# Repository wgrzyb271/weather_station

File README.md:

# 🌡️ ESP32-C6 Indoor Weather Station

An open-source indoor environmental monitoring system built on a custom **ESP32-C6-WROOM-1** dev board. It measures temperature, relative humidity, barometric pressure, and air quality (IAQ) using the **Bosch BME680**, displaying real-time metrics on a color TFT screen with dynamic, flicker-free backlight dimming.

Designed using **KiCad** for hardware development and programmed via **PlatformIO**.

---

## ✨ Features

* **Environmental Sensing:** High-accuracy indoor temperature, humidity, barometric pressure, and Gas/IAQ metrics via Bosch BME680.
* **Dynamic Backlight Control:** Ambient light-sensing using a photoresistor (LDR) voltage divider coupled with high-frequency PWM.
* **IEEE 1789 Compliant Dimming:** Backlight PWM frequency tuned to prevent visible flicker and health risks associated with LED dimming, as outlined in the IEEE 1789-2015 standard.
* **Custom Hardware:** Tailored PCB designed from scratch around the ESP32-C6 module.
* **TFT Display UI:** Real-time data visualization on a vibrant color LCD screen.
* **3D-Printed Enclosure:** Protective cover for the circuit designed in **FreeCAD**, sized to fit the custom PCB and TFT cutout.

---

## 🛠️ Hardware Overview

| Component | Details |
|---|---|
| **Microcontroller** | ESP32-C6-WROOM-1 (RISC-V 32-bit single-core, Wi-Fi 6, Bluetooth 5, 802.15.4 / Thread / Zigbee) |
| **Environmental Sensor** | Bosch BME680 (I2C) |
| **Display** | ST7735 TFT Display (SPI) |
| **Light Sensing** | Photoresistor (LDR) in a voltage divider network connected to an ESP32-C6 ADC pin |
| **Backlight Control** | TFT backlight pin driven directly via the ESP32-C6 **LEDC (LED Control)** peripheral to generate high-frequency PWM for IEEE 1789-compliant dimming |

---

## 💻 Tech Stack & Libraries

* **EDA / Hardware:** [KiCad](https://www.kicad.org/) (Schematics & PCB Layout)
* **3D CAD / Enclosure:** [FreeCAD](https://www.freecad.org/) (Circuit cover / enclosure design)
* **Firmware Framework:** [PlatformIO](https://platformio.org/) on Arduino Core
* **Core Libraries:**
  * `Adafruit_ST7735` & `Adafruit_GFX` – Display driver and graphics library
  * `Adafruit_BME680` & `Adafruit_Sensor` – Environmental sensor driver
  * `Wire.h` & `SPI.h` – Hardware bus communication

---

## 📋 Project Management

This project is managed using [Plane](https://app.plane.so) — an open-source Jira/Confluence alternative — for issue tracking, sprints, and documentation. Feature requests, bugs, and task boards live there rather than solely in GitHub Issues.

---

## 🗺️ Roadmap / Planned Features

* **Zephyr RTOS Port:** Migrate firmware from Arduino Core to Zephyr RTOS for improved power management, native threading, and better long-term driver support on the ESP32-C6.
* **MQTT Broker Integration:** Publish sensor readings (temperature, humidity, pressure, IAQ) to an MQTT broker, with support for **Home Assistant** MQTT auto-discovery.
* **OTA Firmware Updates:** Over-the-air update support to avoid re-flashing over USB for field-deployed units.
* **Web Configuration Portal:** Captive-portal Wi-Fi provisioning and settings UI served directly from the ESP32-C6.
* **Historical Data Logging:** Local logging (SD card or flash) with optional export/graphing.

> Have a feature request? Open an [issue](../../issues) or start a [discussion](../../discussions).

---

## 🚀 Getting Started

### 1. Hardware Design

Schematics, PCB layout files, and BOM (Bill of Materials) can be found in the [`/hardware`](./hardware) directory. Open them with **KiCad 10.0+**.

### 2. Firmware Compilation

1. Install [Visual Studio Code](https://code.visualstudio.com/) and the [PlatformIO extension](https://platformio.org/platformio-ide).
2. Clone this repository:
   ```bash
   git clone https://github.com/your-username/your-repo-name.git
   cd your-repo-name
   ```
3. Open the project folder in VS Code — PlatformIO should detect the `platformio.ini` automatically and install the required libraries and toolchain.
4. Connect the ESP32-C6-WROOM-1 board via USB.
5. Build and upload:
   ```bash
   pio run --target upload
   ```
6. Monitor serial output:
   ```bash
   pio device monitor
   ```

---

## 📁 Repository Structure

```
.
├── hardware/        # KiCad schematics, PCB layout, and BOM
├── enclosure/        # FreeCAD source files and exported STL/STEP for the cover
├── src/              # Firmware source code
├── include/          # Header files
├── lib/               # Project-specific libraries
├── platformio.ini    # PlatformIO project configuration
└── README.md
```

---

## 🤝 Contributing

Contributions, issues, and feature requests are welcome. Feel free to check the [issues page](../../issues) or submit a pull request.

---

## 📄 License

This project is licensed under the terms of the license included in this repository — see [`LICENSE`](./LICENSE) for details.

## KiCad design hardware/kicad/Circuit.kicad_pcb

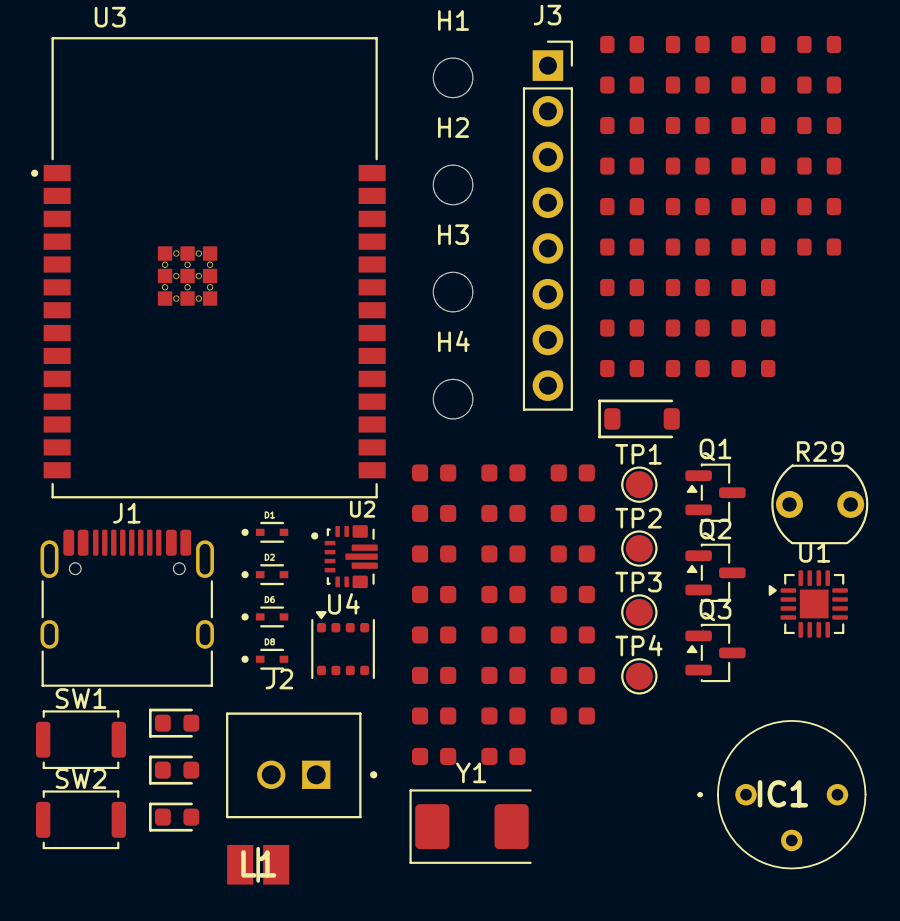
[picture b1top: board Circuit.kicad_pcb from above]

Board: 2 copper layers, 88 parts (0 on the bottom side), 53 nets, no tracks yet.

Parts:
C1, C10, C15, C19: 1uF; C_0603
C2, C3, C5: 4.7uF; C_0603
C4, C6: 2.2uF; C_0603
C7, C8, C9, C16: 10uF; C_0603
C11, C13, C14, C17, C18, C20, C23: 100nF; C_0603
C12: 22uF; C_0603
C21, C22: 12pF; C_0603
D1, D2, D6, D8: LESD5D5.0CT1G; TVS_LESD5D5.0CT1G
D3: Green; D_0603
D4: Red; D_0603
D5: BZT52C6V2; D_SOD-123
D7: Blue; D_0603
H1, H2, H3, H4: MountingHole; MountingHole_2.2mm_M2
IC1: AS312
J1: USB_C_Receptacle_USB2.0_14P; USB_C_Receptacle_HRO_TYPE-C-31-M-12
J2: B2B-XH-A__LF__SN_; JST_B2B-XH-A__LF__SN_
J3: Conn_01x08_Socket; PinSocket_1x08_P2.54mm_Vertical
L1: 1.5uH 4A; INDC2520X100N
Q1, Q2: AO3401A; SOT-23
Q3: AO3400A; SOT-23
R1: 75K; R_0603
R2: 1.6K; R_0603
R3: 1.78K; R_0603
R4, R5: 5k1; R_0603
R6, R14: 470K; R_0603
R7, R8: 1.5K; R_0603
R9, R10, R11, R12, R16, R21, R22, R25, R26: 100K; R_0603
R13, R18, R19, R20, R24: 10K; R_0603
R15: 150K; R_0603
R17: 1K; R_0603
R23: 220; R_0603
R27: 330; R_0603
R28, R31, R32: 4.7K; R_0603
R29: R_Photo; R_LDR_5.1x4.3mm_P3.4mm_Vertical
R30: 30K; R_0603
R33: 10M; R_0603
SW1, SW2: SW_Push; SW_Push_SPST_NO_Alps_SKRK
TH1: 10K; R_0603
TP1: TP_SYS; TestPoint_Pad_D1.5mm
TP2: TP_VBUS; TestPoint_Pad_D1.5mm
TP3, TP4: TP_+3V3; TestPoint_Pad_D1.5mm
U1: BQ24075RGT; VQFN-16-1EP_3x3mm_P0.5mm_EP1.6x1.6mm
U2: TPS63070RNMR; VREG_TPS63070RNMR
U3: ESP32-C6-WROOM-1-N8; XCVR_ESP32-C6-WROOM-1-N8
U4: BME680; Bosch_LGA-8_3x3mm_P0.8mm_ClockwisePinNumbering
Y1: 32.768 kHz; Crystal_SMD_0603-2Pin_6.0x3.5mm

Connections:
+3.3V: C8.1, C12.1, C16.2, C17.2, C18.2, C19.1, C20.1, C23.1, D8.2, IC1.1 (VDD), J3.6, R14.1, R16.1, R17.1, R20.1, R27.1, R28.2, R29.1, R31.1, R32.1, TP3.1 (1_1), U2.7_8 (VOUT), U3.2 (3V3), U4.2 (CSB), U4.6 (VDDIO), U4.8 (VDD)
+5V: C1.1, C2.2, C6.2, D5.1, D6.2, Q1.2 (S), R25.1, TP2.1 (1_1), U1.13 (IN)
BAT: C5.1, J2.1, Q2.2 (S), R11.1, U1.2 (BAT), U1.3 (BAT)
BAT_ADC: C10.2, C11.2, R9.2, R10.1, U3.26 (IO3)
BAT_CTRL: R12.1, U3.12 (IO11)
BL: J3.7, Q3.3 (D), R28.1
CHG_EN1: R21.1, U1.6 (EN1), U3.27 (IO2)
CHG_EN2: R22.1, U1.5 (EN2), U3.24 (RXD0/GPIO17)
D+: D2.2, J1.A6 (D+), J1.B6 (D+), U3.14 (IO13)
D-: D1.2, J1.A7 (D-), J1.B7 (D-), U3.13 (IO12)
DPM_OUT: C3.1, C7.1, C9.1, D3.2, D4.2, R13.1, TP1.1 (1_1), U1.10 (OUT), U1.11 (OUT), U2.12_13 (VIN)
FB: R14.2, R15.1, U2.5 (FB)
GND: C1.2, C2.1, C3.2, C4.1, C5.2, C6.1, C7.2, C8.2, C9.2, C10.1, C11.1, C12.2, C13.2, C14.2, C15.2, C16.1, C17.1, C18.1, C19.2, C20.2, C21.1, C22.1, C23.2, D1.1, D2.1, D6.1, D8.1, IC1.3 (VSS), J1.A1 (GND), J1.A12 (GND), J1.B1 (GND), J1.B12 (GND), J1.SH (SHIELD), J2.2, J3.8, Q3.2 (S), R1.1, R4.2, R5.2, R6.2, R10.2, R15.2, R19.2, R21.2, R22.2, R24.1, R26.2, R30.1, SW1.1, SW2.2, TH1.2, U1.8 (VSS), U1.17 (VSS), U2.4 (GND), U2.6 (FB2), U2.10 (PGND), U2.15 (VSEL), U3.1 (GND), U3.28 (GND), U3.29_1 (GND), U3.29_2 (GND), U3.29_3 (GND), U3.29_4 (GND), U3.29_5 (GND), U3.29_6 (GND), U3.29_7 (GND), U3.29_8 (GND), U3.29_9 (GND), U4.1 (GND), U4.5 (SDO), U4.7 (GND)
LDR: R29.2, R30.2, U3.4 (IO4)
unnamed: D3.1, R7.1
unnamed: D4.1, R8.1
unnamed: D7.2, R27.2
unnamed: IC1.2 (REL), R18.2, R19.1
unnamed: J1.A5 (CC1), R5.1
unnamed: J1.B5 (CC2), R4.1
unnamed: J1.A4 (VBUS), J1.A9 (VBUS), J1.B4 (VBUS), J1.B9 (VBUS), Q1.3 (D)
unnamed: C4.2, D5.2, Q1.1 (G), R6.1
unnamed: Q2.3 (D), R9.1
unnamed: Q2.1 (G), R11.2, R12.2
unnamed: Q3.1 (G), R23.2, R24.2
unnamed: R2.2, U1.12 (ILIM)
unnamed: R3.2, U1.16 (ISET)
unnamed: R2.1, R3.1, U1.4 (~CE), U1.15 (SYSOFF)
unnamed: R1.2, U1.14 (TMR)
unnamed: TH1.1, U1.1 (TS)
unnamed: R13.2, U2.1 (PS/SYNC), U2.14 (EN)
unnamed: L1.2, U2.11 (L1)
unnamed: L1.1, U2.9 (L2)
unnamed: C13.1, U2.3 (VAUX)
unnamed: C14.1, C15.1, R20.2, SW1.2, U3.3 (EN)
unnamed: R17.2, U3.10 (IO8)
unnamed: SW2.1, U3.15 (IO9)
unnamed: D7.1, U3.16 (IO18)
PG: R16.2, U2.2 (PG)
PIR: R18.1, U3.17 (IO19)
PWM: R23.1, U3.23 (IO15)
S_SCL: R32.2, U3.7 (IO7), U4.4 (SCK)
S_SDA: R31.2, U3.6 (IO6), U4.3 (SDI)
TFT_CLK: J3.5, U3.18 (IO20)
TFT_CS: J3.2, U3.11 (IO10)
TFT_DIN: J3.4, U3.19 (IO21)
TFT_D/C: J3.3, U3.20 (IO22)
TFT_RST: J3.1, U3.21 (IO23)
VBUS_SENSE: R25.2, R26.1, TP4.1 (1_1), U3.5 (IO5)
XTAL_N: C21.2, R33.2, U3.9 (IO1), Y1.1
XTAL_P: C22.2, R33.1, U3.8 (IO0), Y1.2
~CHG: R8.2, U1.9 (~CHG)
~PGOOD: R7.2, U1.7 (~PGOOD)

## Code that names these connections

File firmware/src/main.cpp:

#include <Arduino.h>
#include <Wire.h>
#include <SPI.h>
#include <cstdio>
#include <cmath>
#include <Adafruit_GFX.h>
#include <Adafruit_ST7735.h>
#include <Adafruit_Sensor.h>
#include <Adafruit_BME680.h>

// --- PIN DEFINITIONS ---
#define TFT_SCLK  19
#define TFT_MOSI  18
#define TFT_CS    21
#define TFT_DC    16
#define TFT_RST   17

#define ADC_PIN   0
#define BL_PIN    1

// --- HARDWARE SPECIFIC ADC SETTINGS (LDR pull-up / resistor pull-down divider) ---
// Wiring: Vcc -> LDR -> ADC_PIN -> R_pulldown -> GND
// Bright light = LDR resistance drops   = node pulled toward Vcc  = HIGH raw ADC
// Dark room    = LDR resistance rises   = node pulled toward GND  = LOW raw ADC
#define ADC_RAW_DARK    150   // Adjust based on Serial log reading in total darkness
#define ADC_RAW_BRIGHT  3600  // Adjust based on Serial log reading under bright light

// --- IEEE 1789 & HARDWARE PWM CONFIGURATION ---
// IEEE Std 1789-2015 does NOT define a single "safe" frequency - it defines a
// risk curve relating modulation frequency to percent flicker (modulation depth):
//   < 90 Hz            : high risk region, avoid regardless of depth
//   90 Hz  - 1250 Hz    : acceptable only at reduced modulation depth
//   > 1250-3000 Hz      : commonly cited as the "low risk / no observable effect"
//                         band even near 100% modulation depth, since above
//                         ~3 kHz the frequency is well past where stroboscopic
//                         and phantom-array effects remain perceptible.
// 24 kHz PWM Frequency:
// 1. Clears every published threshold above (1250 Hz / 2000 Hz / 3000 Hz) by
//    an 8-24x margin, independent of the exact modulation depth achieved below.
// 2. Sits safely above 20 kHz, the traditional edge of adult human hearing,
//    giving margin against audible coil/capacitor whine (20 kHz itself is
//    borderline - some younger listeners perceive close to that edge).
#define PWM_FREQ          24000  // 24 kHz (comfortable margin above IEEE 1789 low-risk band and audible range)
#define PWM_RES           8      // 8-bit resolution (0 - 255)
#define PWM_MAX           190    // Maximum duty cycle value (for 8-bit resolution)
#define PWM_MIN_THRESHOLD 15     // Duty cycle floor (prevents display dropouts).
                                 // NOTE: this caps modulation depth at ~88.9%
                                 // (Percent Flicker = 100*(PWM_MAX-15)/(PWM_MAX+15)),
                                 // not full 0-100% - a small extra safety
                                 // margin on top of the frequency margin above.

// --- TIMING INTERVALS (Non-Blocking Scheduler) ---
constexpr uint32_t BACKLIGHT_INTERVAL_MS = 20;   // 50 Hz Backlight & Light sensor update rate
constexpr uint32_t SENSOR_INTERVAL_MS    = 2000; // 0.5 Hz Weather updates

// --- GLOBAL OBJECTS ---
Adafruit_ST7735 tft = Adafruit_ST7735(TFT_CS, TFT_DC, TFT_MOSI, TFT_SCLK, TFT_RST);
Adafruit_BME680 bme(&Wire);

// --- STATE MANAGEMENT ---
struct SensorData {
  float temp = 0.0f;
  float hum  = 0.0f;
  float press = 0.0f;
  float gas  = 0.0f;
} currentReadings;

char strBuffer[32];
float filteredAdc = 0.0f; // EMA low-pass filter state variable

// --- HELPER FUNCTIONS ---
const char* evaluateGasQuality(float gasResistance) {
  if (std::isnan(gasResistance) || gasResistance <= 0.0f) return "WarmUp";
  if (gasResistance >= 150000.0f) return "Swietna";
  if (gasResistance >= 80000.0f)  return "Dobra";
  if (gasResistance >= 40000.0f)  return "Srednia";
  if (gasResistance >= 15000.0f)  return "Zla";
  return "Terrible";
}

uint16_t getGasColor(float gasResistance) {
  if (std::isnan(gasResistance) || gasResistance <= 0.0f) return ST77XX_YELLOW;
  if (gasResistance >= 80000.0f)  return ST77XX_GREEN;
  if (gasResistance >= 40000.0f)  return ST77XX_YELLOW;
  if (gasResistance >= 15000.0f)  return ST77XX_ORANGE;
  return ST77XX_RED;
}

void initDisplayUI() {
  tft.initR(INITR_BLACKTAB);
  tft.setRotation(1);
  tft.fillScreen(ST77XX_BLACK);
  tft.drawRect(2, 2, 156, 124, ST77XX_WHITE);
  tft.setTextWrap(false);

  // Header
  tft.setTextColor(ST77XX_CYAN);
  tft.setTextSize(1);
  tft.setCursor(20, 10);
  tft.println("STACJA METEO BME680");
  tft.drawFastHLine(5, 22, 150, ST77XX_CYAN);

  // Static Labels
  tft.setTextColor(ST77XX_WHITE);
  tft.setCursor(10, 35); tft.print("Temperatura:");
  tft.setCursor(10, 55); tft.print("Wilgotnosc :");
  tft.setCursor(10, 75); tft.print("Cisnienie  :");
  tft.setCursor(10, 95); tft.print("Jak. pow.  :");
}

// --- TASK MANAGERS ---
void updateBacklightTask() {
  int rawAdc = analogRead(ADC_PIN);

  // Exponential Moving Average filter (Alpha = 0.05) to eliminate high-frequency noise
  filteredAdc = (0.05f * rawAdc) + (0.95f * filteredAdc);

  // ---------------------------------------------------------
  // MAPPING logic for LDR pull-up divider:
  // Low raw ADC  (dark room)   -> PWM_MAX (full brightness)
  // High raw ADC (bright room) -> PWM_MIN_THRESHOLD (dim)
  // ---------------------------------------------------------
  int targetPwm = map((int)filteredAdc, ADC_RAW_DARK, ADC_RAW_BRIGHT, PWM_MAX, PWM_MIN_THRESHOLD);

  targetPwm = constrain(targetPwm, PWM_MIN_THRESHOLD, PWM_MAX);
  snprintf(strBuffer, sizeof(strBuffer), "%.1d", targetPwm);
  Serial.println(strBuffer);

  // Write PWM duty cycle using ESP32 LEDC peripheral (frequency fixed at
  // PWM_FREQ regardless of duty - only duty cycle varies, never frequency,
  // which avoids the known failure mode where cheap dimmers drop PWM
  // frequency at low brightness and reintroduce flicker risk).
  ledcWrite(BL_PIN, targetPwm);
}

void updateSensorTask() {
  if (!bme.performReading()) {
    Serial.println("[ERROR] BME680 Read Failed!");
    return;
  }

  currentReadings.temp  = bme.temperature;
  currentReadings.hum   = bme.humidity;
  currentReadings.press = bme.pressure / 100.0f;
  currentReadings.gas   = bme.gas_resistance;

  // 1. Temperature
  tft.setTextColor(ST77XX_RED, ST77XX_BLACK);
  tft.setCursor(90, 35);
  snprintf(strBuffer, sizeof(strBuffer), "%.1f C ", currentReadings.temp);
  tft.print(strBuffer);

  // 2. Humidity
  tft.setTextColor(ST77XX_BLUE, ST77XX_BLACK);
  tft.setCursor(90, 55);
  snprintf(strBuffer, sizeof(strBuffer), "%.1f %% ", currentReadings.hum);
  tft.print(strBuffer);

  // 3. Pressure
  tft.setTextColor(ST77XX_GREEN, ST77XX_BLACK);
  tft.setCursor(90, 75);
  snprintf(strBuffer, sizeof(strBuffer), "%.1f hPa", currentReadings.press);
  tft.print(strBuffer);

  // 4. Gas / Air Quality
  const char* statusStr = evaluateGasQuality(currentReadings.gas);
  uint16_t statusColor = getGasColor(currentReadings.gas);

  tft.setTextColor(statusColor, ST77XX_BLACK);
  tft.setCursor(90, 95);
  snprintf(strBuffer, sizeof(strBuffer), "%-9s", statusStr);
  tft.print(strBuffer);

  // Telemetry output over Serial
  Serial.printf("[TELEMETRY] T:%.1f C | H:%.1f %% | P:%.1f hPa | Gas: %s (%.0f Ohm) | Light ADC: %.0f\n",
                currentReadings.temp, currentReadings.hum, currentReadings.press, 
                statusStr, std::isnan(currentReadings.gas) ? 0.0f : currentReadings.gas, filteredAdc);
}

// --- SETUP & MAIN LOOP ---
void setup() {
  Serial.begin(115200);

  // Attach hardware LEDC PWM timer for IEEE 1789 compliance (24 kHz, 8-bit)
  ledcAttach(BL_PIN, PWM_FREQ, PWM_RES);

  Wire.begin();
  initDisplayUI();

  if (!bme.begin()) {
    Serial.println("[CRITICAL] BME680 Sensor initialization failed!");
    tft.drawRect(2, 2, 156, 124, ST77XX_RED);
    tft.setTextColor(ST77XX_RED);
    tft.setTextSize(1);
    tft.setCursor(20, 50);
    tft.println("CRITICAL ERROR:");
    tft.setCursor(20, 65);
    tft.println("BME680 NOT FOUND");
    while (true) { delay(100); }
  }

  // Sensor parameters
  bme.setTemperatureOversampling(BME680_OS_8X);
  bme.setHumidityOversampling(BME680_OS_2X);
  bme.setPressureOversampling(BME680_OS_4X);
  bme.setIIRFilterSize(BME680_FILTER_SIZE_3);
  bme.setGasHeater(320, 150); // 320°C for 150 ms

  // Pre-seed ADC filter with initial pin reading
  filteredAdc = analogRead(ADC_PIN);
}

void loop() {
  uint32_t currentMillis = millis();
  static uint32_t lastBacklightUpdate = 0;
  static uint32_t lastSensorUpdate    = 0;

  // Task 1: Non-blocking Light sensing & PWM adjustment (50 Hz)
  if (currentMillis - lastBacklightUpdate >= BACKLIGHT_INTERVAL_MS) {
    lastBacklightUpdate = currentMillis;
    updateBacklightTask();
  }

  // Task 2: Non-blocking Environmental Measurement processing (0.5 Hz)
  if (currentMillis - lastSensorUpdate >= SENSOR_INTERVAL_MS) {
    lastSensorUpdate = currentMillis;
    updateSensorTask();
  }
}
